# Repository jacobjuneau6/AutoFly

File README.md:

# AutoFly
A cheap, light and, small autonomus drone with ~100g payload capacity and ardupilot
# Why
I made AutoFly as a successor to a pevious autonomus quadcopter that was not able to fly due to low power budgeting. With bigger motors and a 4X larger battery it should fly perfectly. I have always liked autonomus drones for the simple fact that it focuses entirely on design and tuning compared to FPV drones where the pilot plays a cirtical role.
# Assembly

# PCB

# External Wiring

# BOM
| Name | Purpose | Quantity | Total Cost (USD) | Link | Distributor |
| --- | --- | --- | --- | --- | --- |
| Custom PCB | hold all of the FC components | 1 | 12.50 |  | PCBWAY |
| Alibaba Shipping Customs and tax | Alibaba Shipping Customs and tax | 1 | 15.45 |  | Alibaba |
| Aliexpress shipping & tax | Aliexpress shipping & tax | 1 | 4.30 |  | Aliexpress |
| Amazon Shipping & TAX | Amazon Shipping & TAX | 1 | 7.67 |  | Amazon |
| M3 screws | hold down various components | 1 | 8.49 | https://www.amazon.com/Self-Tapping-Screws-Phillips-Carbon-Plastic/dp/B0BPM8J5F5 | Amazon |
| Deans T connectors | battery connector | 1 | 1.75 | https://www.aliexpress.us/item/3256806681263722.html?utparam-url=scene%3Asearch%7Cquery_from%3A%7Cx_object_id%3A1005006867578474%7C_p_origin_prod%3A | Aliexpress |
| 1mm pitch connectors | allows connecting standard drone peripherals to the FC | 1 | 13.22 | https://www.digikey.com/en/products/detail/pololu/4772/19529079 | Digikey |
| APM2.5 power monitor | measures the power and current off the battery to enter failsafe mode when battery about to die | 1 | 9.99 | https://www.amazon.com/Pixhawk-BEC-Helicopter-Quadcopters-Accessories/dp/B0BCJQR3YN?th=1 | Amazon |
| 3S lipo battery | powers the drone | 1 | 14.24 | https://www.amazon.com/OVONIC-Airplane-Quadcopter-Helicopter-Multi-Motor/dp/B077P73SDS?th=1 | Amazon |
| Propellers | provides the motors a way to generate lift | 1 | 16.99 | https://www.amazon.com/uxcell-Propellers-Quadcopter-Airplane-Adapter/dp/B07QK5CXK8 | Amazon |
| Power distribution board | sends power from the battery to all 4 escs | 1 | 4.51 | https://www.aliexpress.us/item/3256806649142265.html?mp=1 | Aliexpress |
| 2205 2300kv brushless motors | allows drone to fly  | 1 | 8.61 | https://www.aliexpress.us/item/3256808432301575.html?utparam-url=scene%3Asearch%7Cquery_from%3A%7Cx_object_id%3A1005008618616327%7C_p_origin_prod%3A | Aliexpress |
| BLHeli-s 20A ESCs | provides power and control to the motor | 1 | 29.61 | https://www.aliexpress.us/item/2255800001568515.html?utparam-url=scene%3Asearch%7Cquery_from%3A%7Cx_object_id%3A4000187883267%7C_p_origin_prod%3A | Aliexpress |
| HGLRC M100-5883 GPS and Compass | Provides location and heading data to the FC | 1 | 18.99 | https://www.amazon.com/HGLRC-M100-5883-GPS-Generation-Compatible/dp/B0CB5N8RQ8 | Amazon |
| ESP32C3 super mini | Provides the transmitter and reciver | 1 | 9.99 | https://www.amazon.com/AITRIP-ESP32-C3-Development-Board-Bluetooth/dp/B0FBGDFPBQ?th=1 | Amazon |
| ICM-42688 IMU |       Tells the drone its orientation and acceleration | 1 | 8.39 | https://www.alibaba.com/product-detail/AI-KSEN-Six-Axis-IMU-Module_1601663823996.html?selectedCarrierCode=SEMI_MANAGED_STANDARD%40%40STANDARD&priceId=8b43f52ef39e4de496b68d31a66a839f | Alibaba |
| GY-BMP280 | provides an altimeter | 1 | 0.43 | https://www.alibaba.com/product-detail/GY-BME280-5V-GY-BMP280-5V_1601291648398.html?selectedCarrierCode=SEMI_MANAGED_STANDARD%40%40STANDARD&priceId=194c7af6cc614cb9b190c4876a9feccd | Alibaba |
| STM32H743VIT6 | Will be the brains of the drone | 1 | 11.80 | https://www.alibaba.com/product-detail/STM32H743VIT6-STM32H750VBT6-STM32-STM32H-STM32H7-Core_1601368312109.html | Alibaba |

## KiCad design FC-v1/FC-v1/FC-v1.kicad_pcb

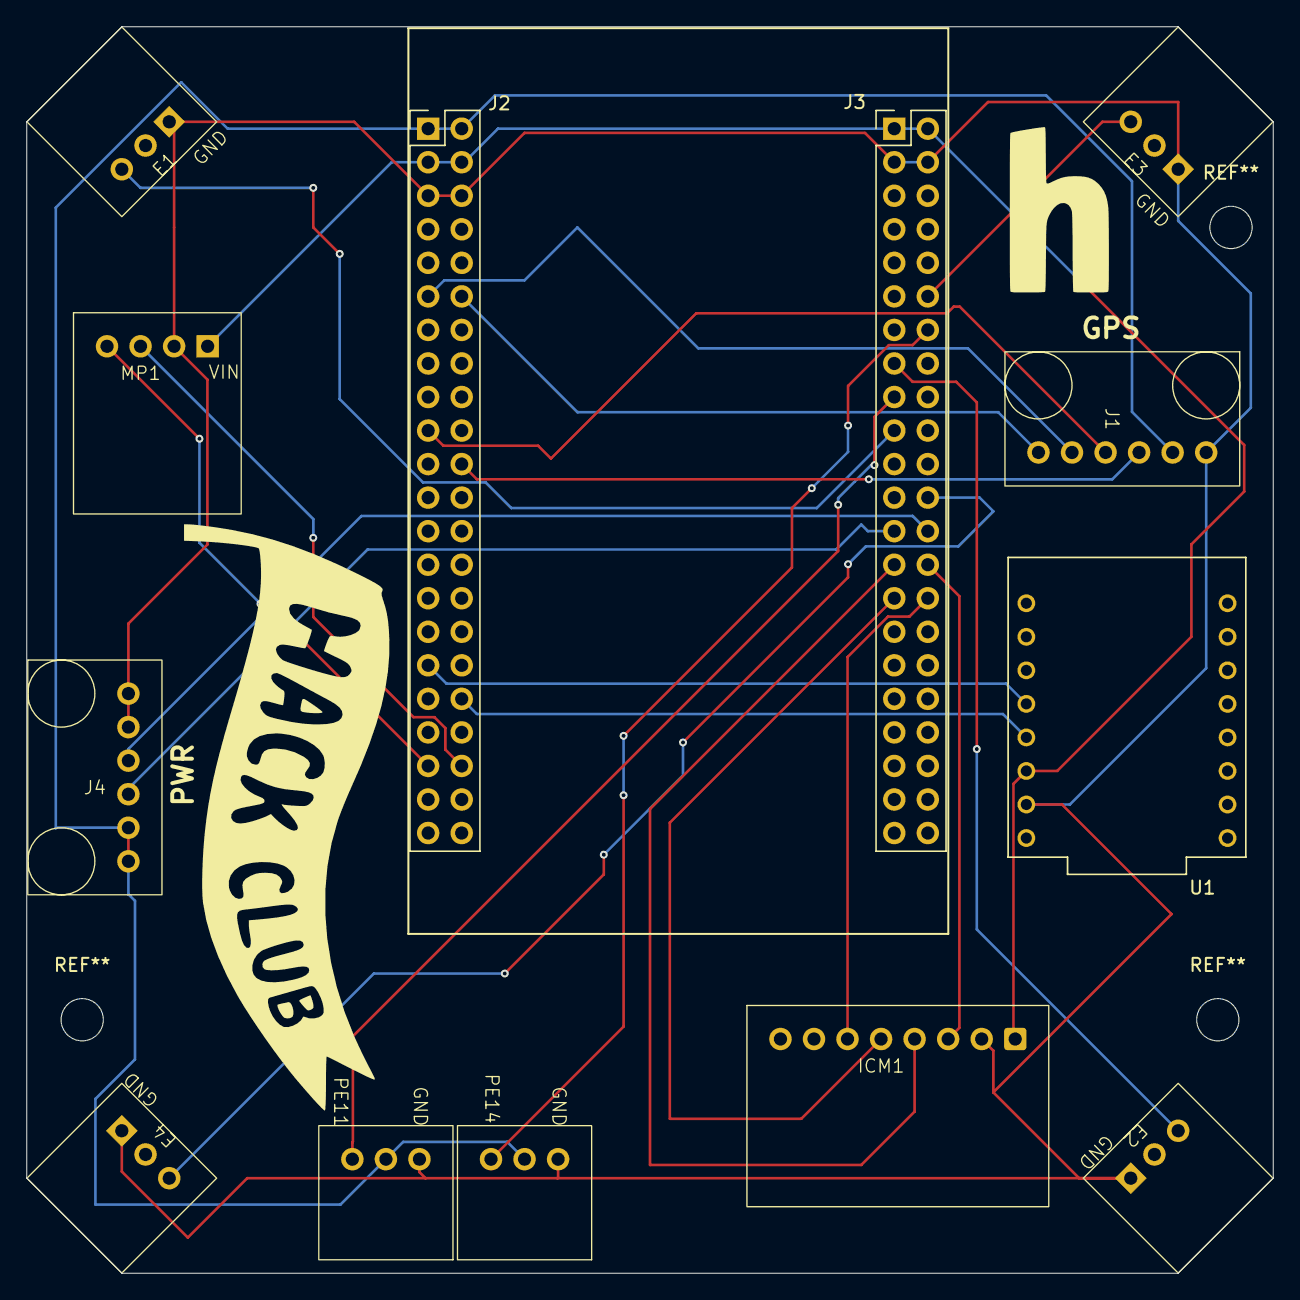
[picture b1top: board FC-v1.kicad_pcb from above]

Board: 2 copper layers, 94.4 x 94.4 mm, 13 parts (0 on the bottom side), 23 nets.

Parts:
E1, E2, E3, E4: ESC-connector
ICM1: ICM42688
J1, J4: 530470610; 4772
J2: Left; PinHeader_2x22_P2.54mm_Vertical
J3: Right; PinHeader_2x22_P2.54mm_Vertical
MP1: BMP280
U1: ESP32-C3_SUPERMINI_TH; MODULE_ESP32-C3_SUPERMINI_TH
U2, U3: Untitled

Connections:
+3.3V: ICM1.1 (VCC), J2.3, J2.4, J3.1, J3.2, MP1.1 (VIN), U1.3.3 (3V3)
+5V: J1.2, J2.1, J2.2, J4.5, J4.6, U2.2 (5V), U3.2 (5V)
/PA4: ICM1.6 (CS), J3.30
/PA5: ICM1.5 (SCLK), J3.29
/PA6: ICM1.3 (MISO), J3.28
/PA7: ICM1.4 (MOSI), J3.27
/PA9_TX1: J1.4, J2.19
/PA10_RX1: J1.3, J2.22
/PB0: E4.1 (SIGNAL), J3.24
/PB6: J2.40, MP1.3 (SCl)
/PB7: J2.39, MP1.4 (SDA)
/PB10: E3.1 (SIGNAL), J3.12
/PC4: J3.26, J4.3
/PC5: J3.25, J4.4
/PD6: J2.33, U1.3 (GPIO3)
/PD7: J2.36, U1.4 (GPIO4)
/PD12: J1.6, J2.12
/PD13: J1.5, J2.11
/PE9: E1.1 (SIGNAL), J3.19
/PE11: J3.17, U2.3 (SIG)
/PE13: E2.1 (SIGNAL), J3.15
/PE14: J3.14, U3.3 (SIG)
GND: E1.2 (GND), E2.2 (GND), E3.2 (GND), E4.2 (GND), ICM1.2 (GND), J1.1, J2.5, J2.6, J3.3, J3.4, J4.1, J4.2, MP1.2 (GND), U1.G (GND), U2.1 (GND), U3.1 (GND)

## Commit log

2026-03-16 add vscodium workspace file
2026-03-19 design and build PCB
2026-03-19 add ardupilot submodule
2026-03-21 CAD files
2026-03-22 Journal BOM Readme Gerbers
